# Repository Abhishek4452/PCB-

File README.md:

# PCB-
here i will updated my all the projects in which i have worked so far please open the BRANCH IN RIGHT CORNER TO GET ACCESS.

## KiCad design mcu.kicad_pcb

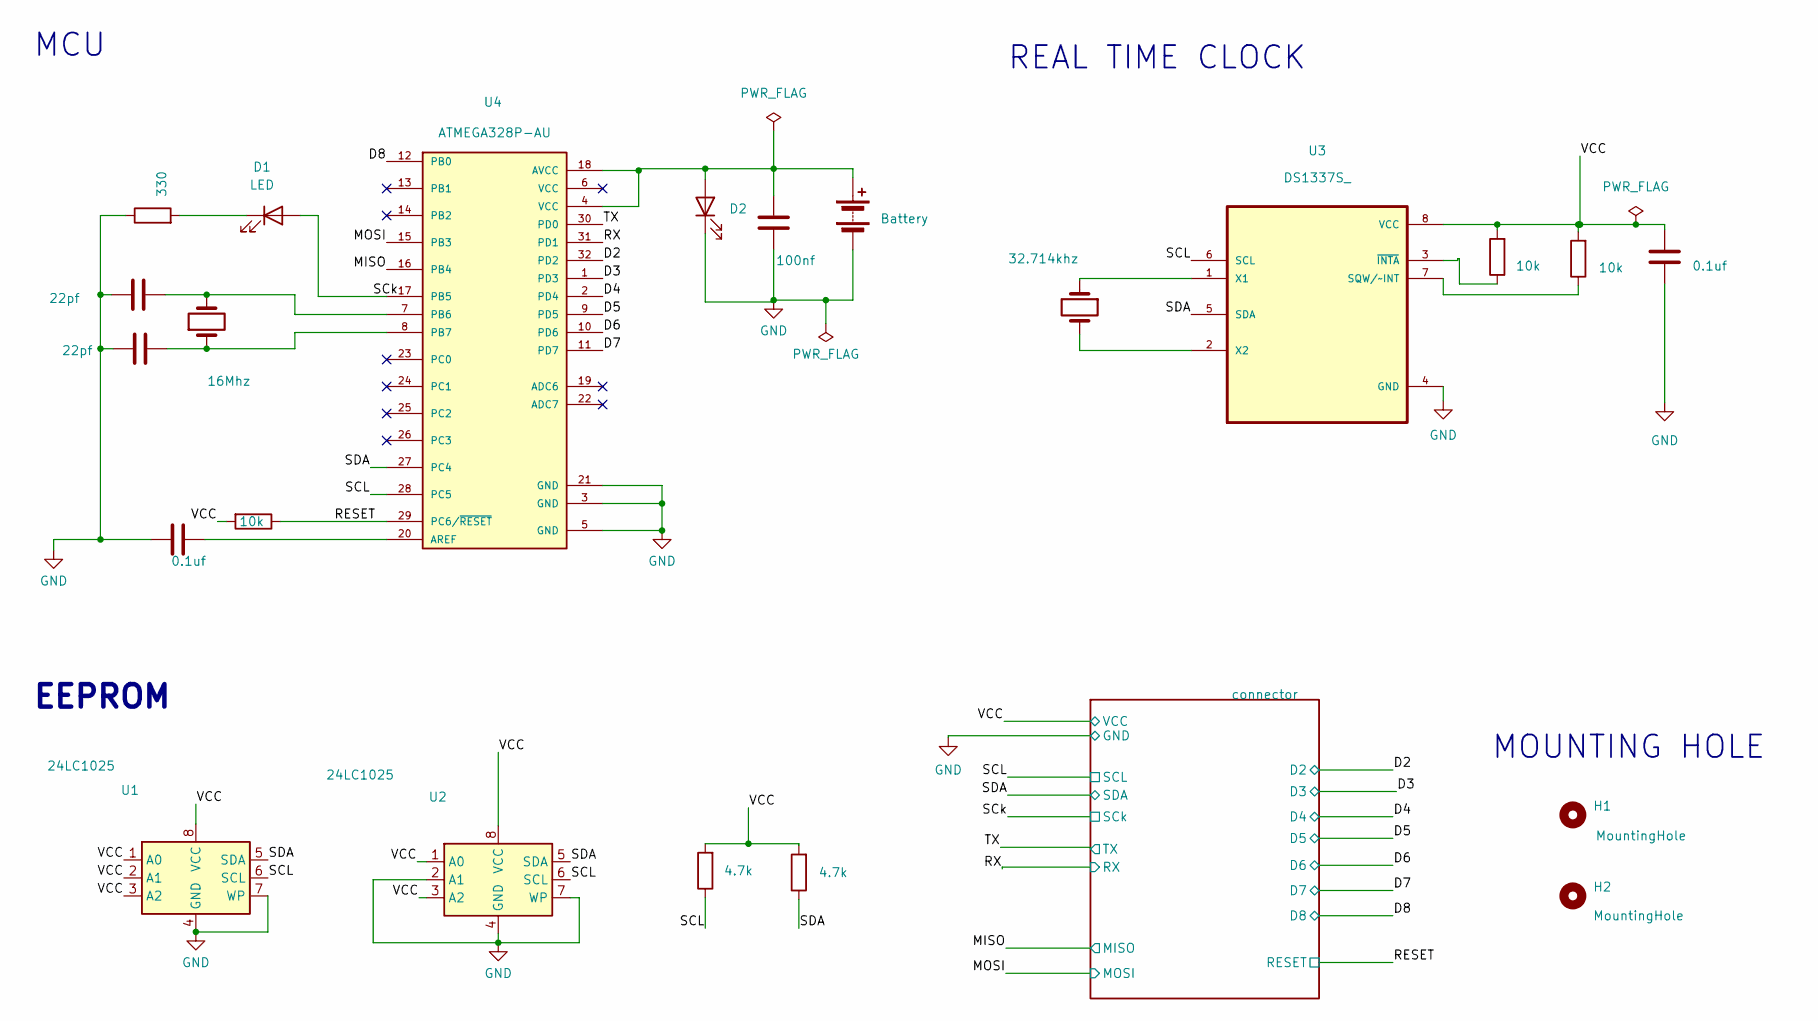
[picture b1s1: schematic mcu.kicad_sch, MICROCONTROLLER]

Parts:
BT1: Battery; PinHeader_1x02_P2.54mm_Vertical
C1, C2: 0.1uf; C_0805_2012Metric_Pad1.18x1.45mm_HandSolder
C3: 100nf; C_0805_2012Metric_Pad1.18x1.45mm_HandSolder
C4, C5: 22pf; C_0805_2012Metric_Pad1.18x1.45mm_HandSolder
D1, D2: LED; LED_0805_2012Metric_Pad1.15x1.40mm_HandSolder
H1, H2: MountingHole; MountingHole_2.1mm
R2: 330; R_0805_2012Metric_Pad1.20x1.40mm_HandSolder
R3, R7: 4.7k; R_0805_2012Metric_Pad1.20x1.40mm_HandSolder
R4, R5, R6: 10k; R_0805_2012Metric_Pad1.20x1.40mm_HandSolder
U1, U2: 24LC1025; TSSOP-8_4.4x3mm_P0.65mm
U3: DS1337S_; SOIC127P600X175-8N
U4: ATMEGA328P-AU; QFP80P900X900X120-32N; PARTREV 8271A; DigiKey_Part_Number ATMEGA328P-AU-ND
Y1: 32.714khz; Oscillator_SMD_Fordahl_DFAS15-4Pin_5.0x3.2mm_HandSoldering
Y2: 16Mhz; Oscillator_SMD_Fordahl_DFAS15-4Pin_5.0x3.2mm_HandSoldering

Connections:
/D2: U4.32 (PD2); also elsewhere on the board
/D3: U4.1 (PD3); also elsewhere on the board
/D4: U4.2 (PD4); also elsewhere on the board
/D5: U4.9 (PD5); also elsewhere on the board
/D6: U4.10 (PD6); also elsewhere on the board
/D7: U4.11 (PD7); also elsewhere on the board
/D8: U4.12 (PB0); also elsewhere on the board
/MISO: U4.16 (PB4); also elsewhere on the board
/MOSI: U4.15 (PB3); also elsewhere on the board
/RESET: R6.1, U4.29 (PC6/~RESET); also elsewhere on the board
/RX: U4.31 (PD1); also elsewhere on the board
/SCL: R7.1, U1.6 (SCL), U2.6 (SCL), U3.6 (SCL), U4.28 (PC5); also elsewhere on the board
/SCk: D1.2 (A), U4.17 (PB5); also elsewhere on the board
/SDA: R3.1, U1.5 (SDA), U2.5 (SDA), U3.5 (SDA), U4.27 (PC4); also elsewhere on the board
/TX: U4.30 (PD0); also elsewhere on the board
/VCC: C2.2, R3.2, R4.2, R5.2, R6.2, R7.2, U1.1 (A0), U1.2 (A1), U1.3 (A2), U1.8 (VCC), U2.1 (A0), U2.3 (A2), U2.8 (VCC), U3.8 (VCC); also elsewhere on the board
GND: BT1.2 (-), C1.1, C2.1, C3.1, C4.2, C5.1, D2.1 (K), R2.1, U1.4 (GND), U1.7 (WP), U2.2 (A1), U2.4 (GND), U2.7 (WP), U3.4 (GND), U4.3 (GND), U4.5 (GND), U4.21 (GND); also elsewhere on the board
unnamed: BT1.1 (+), C3.2, D2.2 (A), U4.4 (VCC), U4.18 (AVCC)
unnamed: D1.1 (K), R2.2
unnamed: R5.1, U3.7 (SQW/~INT)
unnamed: U3.1 (X1), Y1.1
unnamed: U3.2 (X2), Y1.2
unnamed: R4.1, U3.3 (~INTA)
unnamed: C1.2, U4.20 (AREF)
unnamed: C4.1, U4.7 (PB6), Y2.2
unnamed: C5.2, U4.8 (PB7), Y2.1

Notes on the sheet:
MCU
REAL TIME CLOCK
EEPROM
MOUNTING HOLE

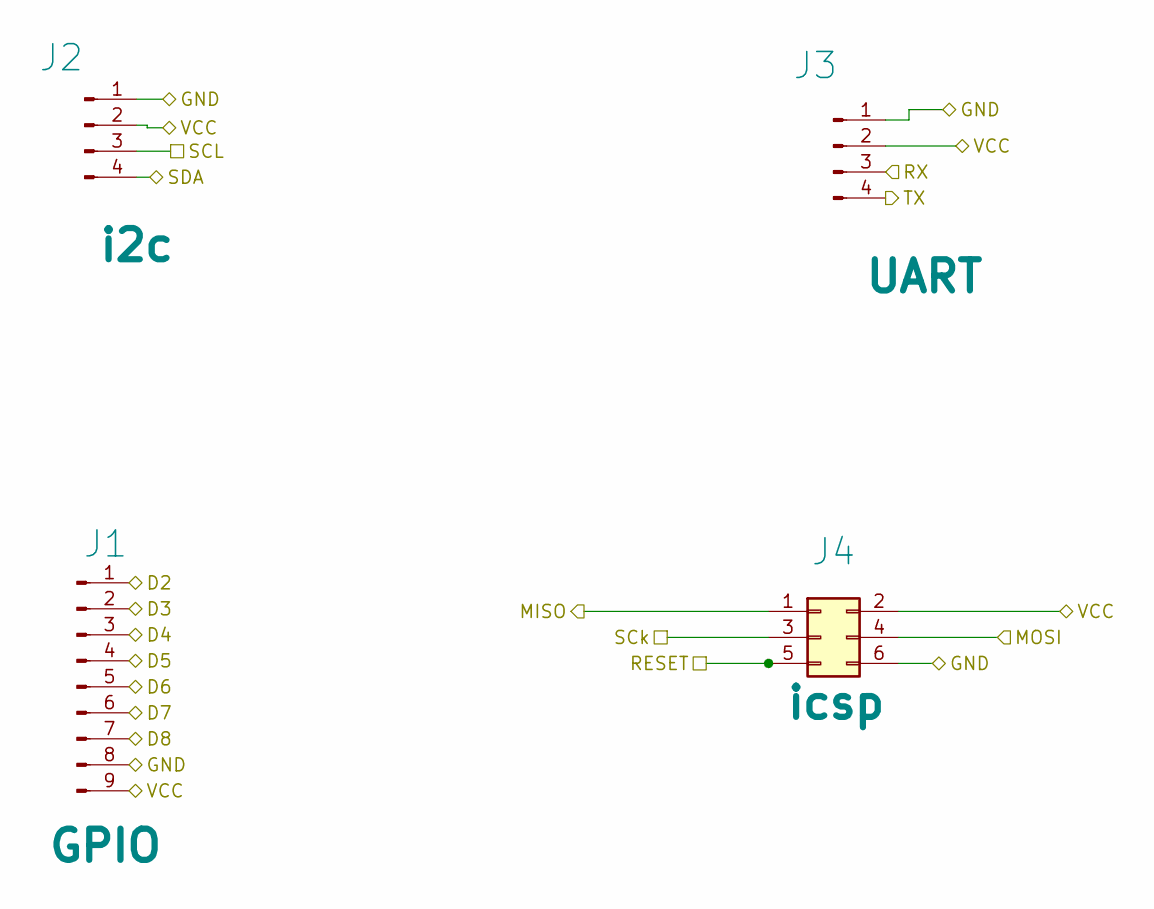
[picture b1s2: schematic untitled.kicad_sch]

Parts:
J1: Conn_01x09_Pin; PinHeader_1x09_P2.54mm_Vertical
J2, J3: Conn_01x04_Pin; PinSocket_1x04_P2.54mm_Vertical
J4: Conn_02x03_Odd_Even; PinHeader_2x03_P2.54mm_Vertical

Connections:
/D2: J1.1; also elsewhere on the board
/D3: J1.2; also elsewhere on the board
/D4: J1.3; also elsewhere on the board
/D5: J1.4; also elsewhere on the board
/D6: J1.5; also elsewhere on the board
/D7: J1.6; also elsewhere on the board
/D8: J1.7; also elsewhere on the board
/MISO: J4.1; also elsewhere on the board
/MOSI: J4.4; also elsewhere on the board
/RESET: J4.5; also elsewhere on the board
/RX: J3.3; also elsewhere on the board
/SCL: J2.3; also elsewhere on the board
/SCk: J4.3; also elsewhere on the board
/SDA: J2.4; also elsewhere on the board
/TX: J3.4; also elsewhere on the board
/VCC: J1.9, J2.2, J3.2, J4.2; also elsewhere on the board
GND: J1.8, J2.1, J3.1, J4.6; also elsewhere on the board

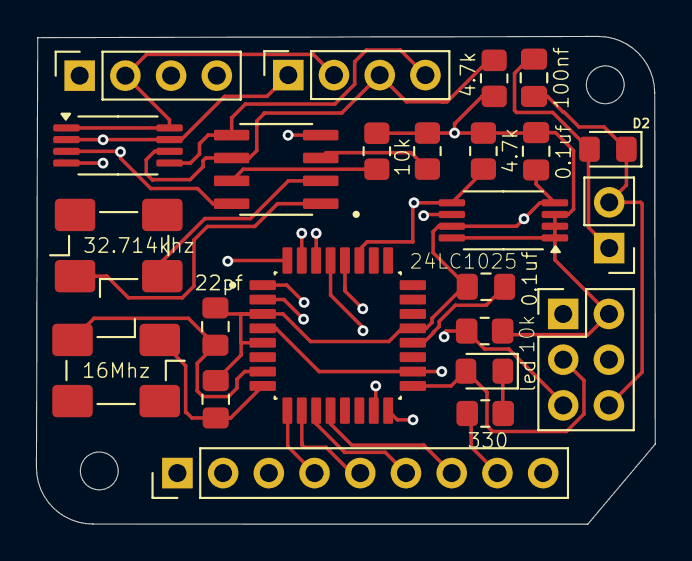
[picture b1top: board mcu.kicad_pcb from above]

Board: 4 copper layers, 34.4 x 27.1 mm, 26 parts (0 on the bottom side), 26 nets.

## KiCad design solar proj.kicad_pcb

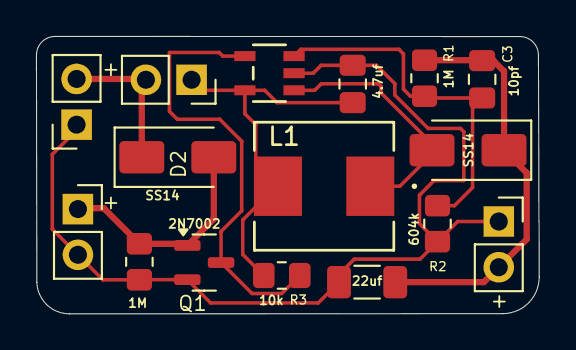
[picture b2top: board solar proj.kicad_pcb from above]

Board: 2 copper layers, 27.9 x 15.4 mm, 16 parts (0 on the bottom side), 8 nets.

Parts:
C1: 4.7uf; C_0805_2012Metric_Pad1.18x1.45mm_HandSolder
C2: 22uf; C_1206_3216Metric_Pad1.33x1.80mm_HandSolder
C3: 10pf; C_0805_2012Metric_Pad1.18x1.45mm_HandSolder
D1, D2: SS14; D_SMA
J1, J2, J3, J4: Conn_01x02_Pin; PinSocket_1x02_P2.54mm_Vertical
L1: ASPI0630L; IND_ASPI-0630LR_ABR
Q1: 2N7002; SOT-23
R1, R4: 1M; R_0805_2012Metric_Pad1.20x1.40mm_HandSolder
R2: 604k; R_0805_2012Metric_Pad1.20x1.40mm_HandSolder
R3: 10k; R_0805_2012Metric_Pad1.20x1.40mm_HandSolder
U1: aktr; SOT23-5_1P55X2P9_DIO

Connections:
/battery_pwr: D2.1 (K), J2.2, J3.2
/output_pwr: C2.1, C3.1, D1.1 (K), J1.2, R1.1
/solar_PWR: D2.2 (A), J4.1, Q1.1 (G), R4.1
GNDD: C1.2, C2.2, J1.1, J2.1, J4.2, Q1.2 (S), R2.2, R4.2, U1.2 (GND)
unnamed: D1.2 (A), L1.1, U1.1 (SW)
unnamed: C1.1, J3.1, L1.2, R3.1, U1.5 (VIN)
unnamed: Q1.3 (D), R3.2, U1.4 (SHDN)
unnamed: C3.2, R1.2, R2.1, U1.3 (FB)

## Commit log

2025-07-25 Add files via upload
    HERE I HAVE UPLOADED A 2 LAYER PCB HAVING AN ARDUINO UNO - MCU
